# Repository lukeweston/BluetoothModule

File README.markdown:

Bluetooth LE module breakout board - uses Laird BL600 Module, provides FT230X USB virtual UART. (USB bridge is optional, can be disconnected and re-patched to other hardware.)

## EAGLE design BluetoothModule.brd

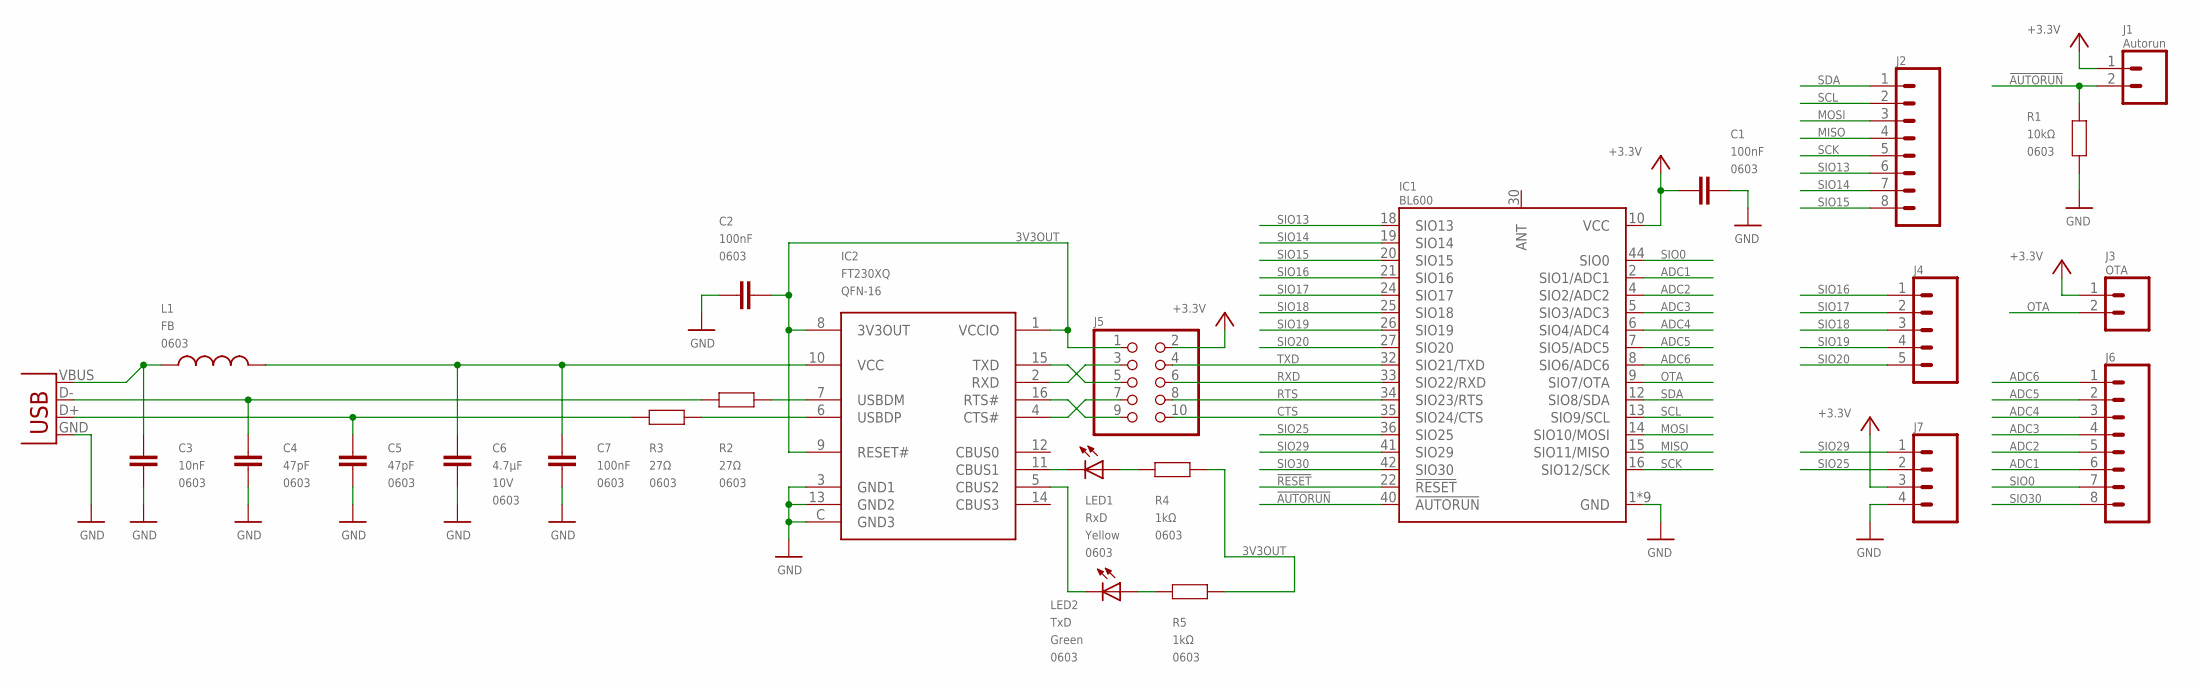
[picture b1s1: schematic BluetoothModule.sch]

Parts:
C1, C2, C7: 100nF; 0603
C3: 10nF; 0603
C4, C5: 47pF; 0603
C6: 4.7µF; 0603; VOLTAGE 10V
IC1: BL600; BL600-SA
IC2: FT230XQ; QFN4X4-16
J1: Autorun; 1X02
J2, J6: M08STD; 1X08
J3: OTA; 1X02
J4: M05PTH; 1X05
J5: PINHD-2X5; 2X05
J7: M04PTH; 1X04
J8: USB; USB-MICROB
L1: FB; 0603
LED1: RxD; LED-0603
LED2: TxD; LED-0603
R1: 10kΩ; 0603
R2, R3: 27Ω; 0603
R4, R5: 1kΩ; 0603

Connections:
3V3OUT: C2.2, IC2.1 (VCCIO), IC2.8 (3V3OUT), IC2.9 (RESET#), J5.1, R4.2, R5.2
!AUTORUN: IC1.40 (!AUTORUN), J1.2, R1.2
!RESET: IC1.22 (!RESET)
+3V3: C1.2, IC1.10 (VCC), J1.1, J3.1, J5.2, J7.3
ADC1: IC1.2 (SIO1/ADC1), J6.6
ADC2: IC1.4 (SIO2/ADC2), J6.5
ADC3: IC1.5 (SIO3/ADC3), J6.4
ADC4: IC1.6 (SIO4/ADC4), J6.3
ADC5: IC1.7 (SIO5/ADC5), J6.2
ADC6: IC1.8 (SIO6/ADC6), J6.1
CTS: IC1.35 (SIO24/CTS), J5.10
GND: C1.1, C2.1, C3.1, C4.1, C5.1, C6.1, C7.1, IC1.1 (GND), IC1.3 (GND), IC1.11 (GND), IC1.17 (GND), IC1.28 (GND), IC1.29 (GND), IC1.31 (GND), IC1.37 (GND), IC1.43 (GND), IC2.3 (GND1), IC2.13 (GND2), IC2.C (GND3), J7.4, J8.GND, R1.1
MISO: IC1.15 (SIO11/MISO), J2.4
MOSI: IC1.14 (SIO10/MOSI), J2.3
unnamed: IC2.4 (CTS#), J5.7
unnamed: IC2.16 (RTS#), J5.9
unnamed: IC2.2 (RXD), J5.3
unnamed: IC2.15 (TXD), J5.5
unnamed: C3.2, J8.VBUS, L1.1
unnamed: LED2.A, R5.1
unnamed: IC2.11 (CBUS1), LED1.C
unnamed: IC2.5 (CBUS2), LED2.C
unnamed: LED1.A, R4.1
unnamed: C6.2, C7.2, IC2.10 (VCC), L1.2
unnamed: C4.2, J8.D-, R2.1
unnamed: C5.2, J8.D+, R3.1
unnamed: IC2.6 (USBDP), R3.2
unnamed: IC2.7 (USBDM), R2.2
OTA: IC1.9 (SIO7/OTA), J3.2
RTS: IC1.34 (SIO23/RTS), J5.8
RXD: IC1.33 (SIO22/RXD), J5.6
SCK: IC1.16 (SIO12/SCK), J2.5
SCL: IC1.13 (SIO9/SCL), J2.2
SDA: IC1.12 (SIO8/SDA), J2.1
SIO0: IC1.44 (SIO0), J6.7
SIO13: IC1.18 (SIO13), J2.6
SIO14: IC1.19 (SIO14), J2.7
SIO15: IC1.20 (SIO15), J2.8
SIO16: IC1.21 (SIO16), J4.1
SIO17: IC1.24 (SIO17), J4.2
SIO18: IC1.25 (SIO18), J4.3
SIO19: IC1.26 (SIO19), J4.4
SIO20: IC1.27 (SIO20), J4.5
SIO25: IC1.36 (SIO25), J7.2
SIO29: IC1.41 (SIO29), J7.1
SIO30: IC1.42 (SIO30), J6.8
TXD: IC1.32 (SIO21/TXD), J5.4

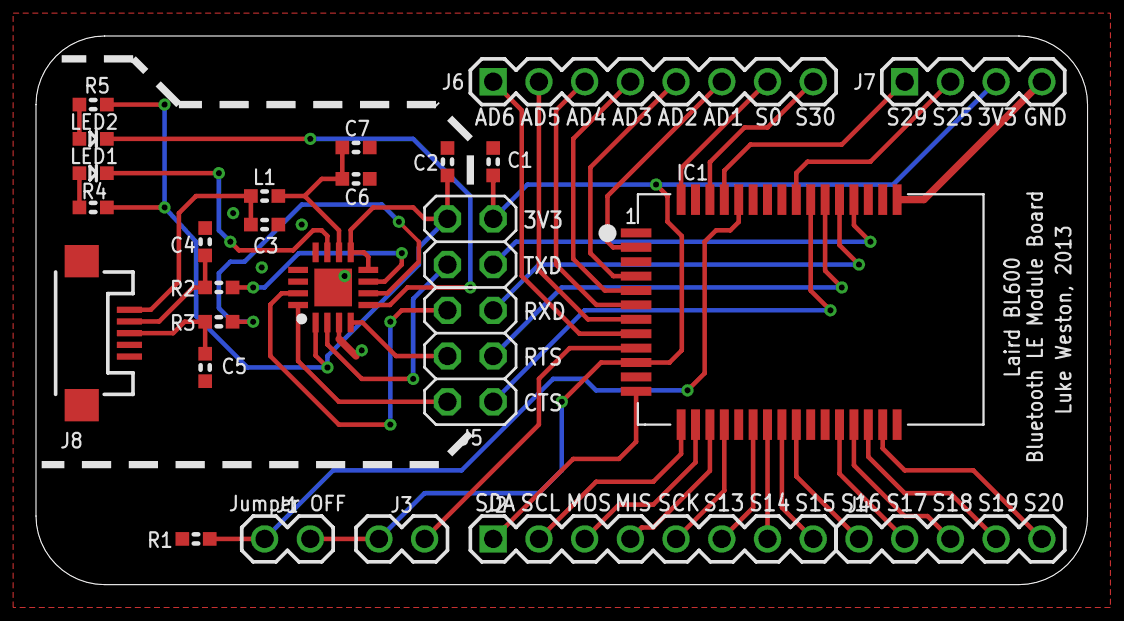
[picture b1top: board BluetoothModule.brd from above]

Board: 2 copper layers, 58.4 x 30.5 mm, 25 parts (0 on the bottom side), 46 nets.

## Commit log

2014-01-17 tweaked USB connector footprint
